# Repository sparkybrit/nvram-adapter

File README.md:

# nvram-adapter

A battery-backed 1M × 8 SRAM board for a breadboard, in the place of the
[ROM/RAM breadboard adapter](https://github.com/sparkybrit/rom-ram-breadboard-adapter) when it carries a
Dallas DS1250AB NVRAM, which is no longer made.

- **U1**: Lyontek LY62W10248ML-55LLI, 1M × 8 SRAM in TSOP-II-44, the chip used on the
  [SRAM breadboard adapter](https://github.com/sparkybrit/sram-breadboard-adapter).
- **U2**: Maxim MAX6365PKA46+T: switches the SRAM to the coin cell when +5 V fails, and blocks chip enable below
  4.63 V, matching the DS1250AB's 4.62 V write protection.
- **BT1**: CR2032 in an MPD BU2032SM-BT-GTR holder.
- **J1, J2**: the ROM/RAM adapter's two 20-pin headers, in the same places and with the same pinout except for
  four pins: J1.20 carries A19 (not +5 V), J2.12 carries U2's open-drain `/RESET`, J2.15 is not connected and J2.18
  is a +5 V input. Every pin is named on the silkscreen.
- **J3**: a screw terminal for +5 V, for when it doesn't come from the breadboard on J2.18.
- **SW1**: a manual reset button on U2's `/MR`.
- **D1**: a power LED.

It is also the prototype for the NVRAM and reset circuit of the Sparky1 backplane's NVRAM card.

KiCad 10, four layers. Built for [Sparky1](https://github.com/sparkybrit/sparky1), a 68030 breadboard computer.

**Status:** schematic done, board placed but not yet routed.

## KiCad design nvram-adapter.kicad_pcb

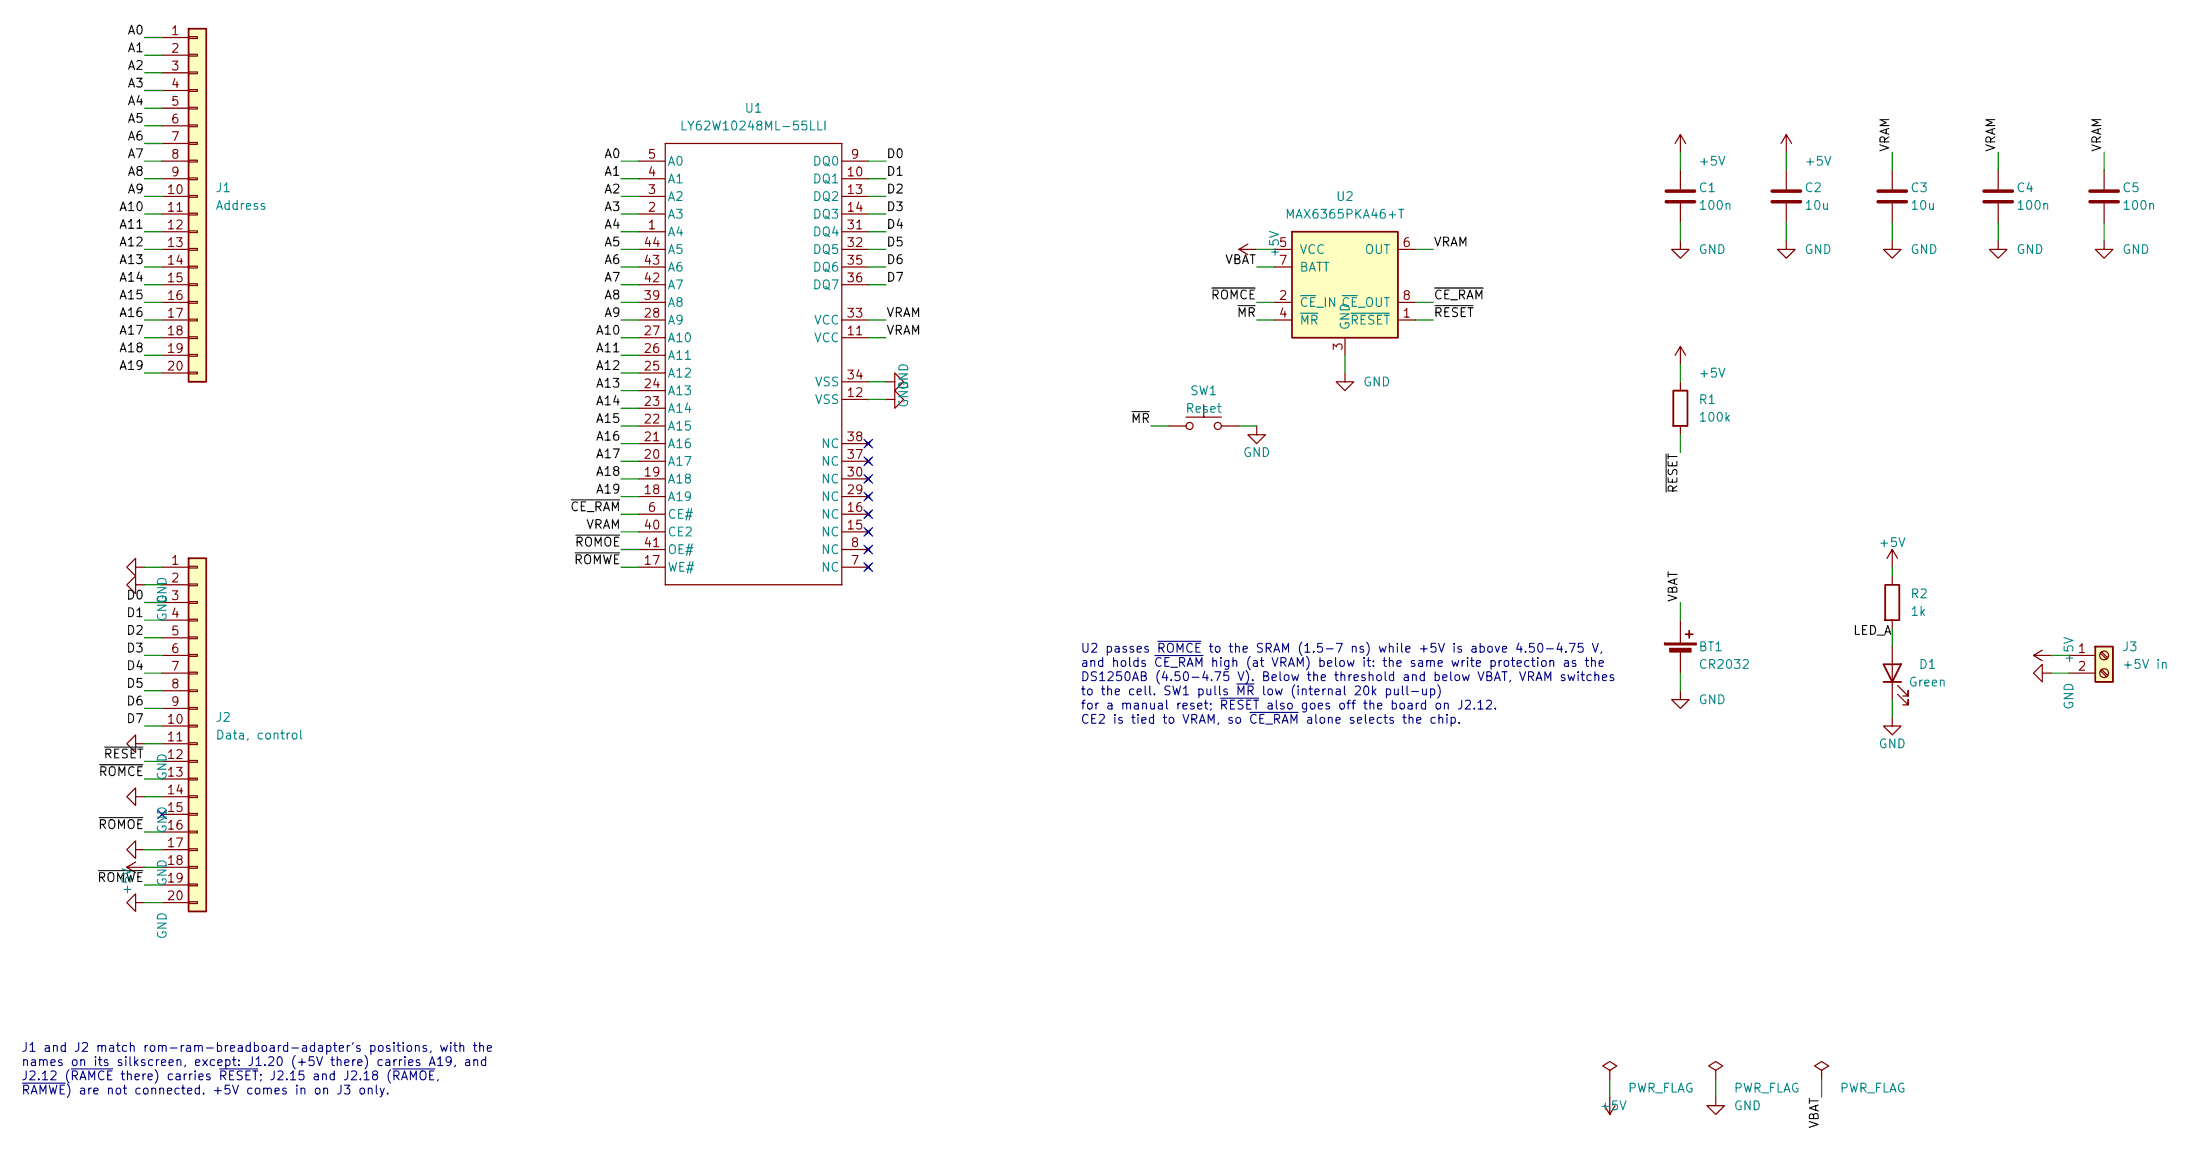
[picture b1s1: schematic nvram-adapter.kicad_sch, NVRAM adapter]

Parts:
BT1: CR2032; BatteryHolder_MPD_BU2032SM-BT_1x2032; MPN BU2032SM-BT-GTR
C1: 100n; C_0603_1608Metric
C2, C3: 10u; C_0805_2012Metric
C4, C5: 100n; C_0402_1005Metric
D1: Green; LED_0603_1608Metric
J1: Address; PinHeader_1x20_P2.54mm_Vertical
J2: Data, control; PinHeader_1x20_P2.54mm_Vertical
J3: +5V in; TerminalBlock_Phoenix_MKDS-1,5-2-5.08_1x02_P5.08mm_Horizont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
R1: 100k; R_0603_1608Metric
R2: 1k; R_0603_1608Metric
SW1: Reset; SW_SPST_PTS810
U1: LY62W10248ML-55LLI; TSOP-II-44_400MIL_LTK
U2: MAX6365PKA46+T; SOT-23-8

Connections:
+5V: C1.1, C2.1, J2.18, J3.1, R1.1, R2.1, U2.5 (VCC)
/A0: J1.1, U1.5 (A0)
/A1: J1.2, U1.4 (A1)
/A2: J1.3, U1.3 (A2)
/A3: J1.4, U1.2 (A3)
/A4: J1.5, U1.1 (A4)
/A5: J1.6, U1.44 (A5)
/A6: J1.7, U1.43 (A6)
/A7: J1.8, U1.42 (A7)
/A8: J1.9, U1.39 (A8)
/A9: J1.10, U1.28 (A9)
/A10: J1.11, U1.27 (A10)
/A11: J1.12, U1.26 (A11)
/A12: J1.13, U1.25 (A12)
/A13: J1.14, U1.24 (A13)
/A14: J1.15, U1.23 (A14)
/A15: J1.16, U1.22 (A15)
/A16: J1.17, U1.21 (A16)
/A17: J1.18, U1.20 (A17)
/A18: J1.19, U1.19 (A18)
/A19: J1.20, U1.18 (A19)
/D0: J2.3, U1.9 (DQ0)
/D1: J2.4, U1.10 (DQ1)
/D2: J2.5, U1.13 (DQ2)
/D3: J2.6, U1.14 (DQ3)
/D4: J2.7, U1.31 (DQ4)
/D5: J2.8, U1.32 (DQ5)
/D6: J2.9, U1.35 (DQ6)
/D7: J2.10, U1.36 (DQ7)
/LED_A: D1.2 (A), R2.2
/VBAT: BT1.1 (+), U2.7 (BATT)
/VRAM: C3.1, C4.1, C5.1, U1.11 (VCC), U1.33 (VCC), U1.40 (CE2), U2.6 (OUT)
/~CE_RAM: U1.6 (CE#), U2.8 (~CE_OUT)
/~MR: SW1.1, U2.4 (~MR)
/~RESET: J2.12, R1.2, U2.1 (~RESET)
/~ROMCE: J2.13, U2.2 (~CE_IN)
/~ROMOE: J2.16, U1.41 (OE#)
/~ROMWE: J2.19, U1.17 (WE#)
GND: BT1.2 (-), C1.2, C2.2, C3.2, C4.2, C5.2, D1.1 (K), J2.1, J2.2, J2.11, J2.14, J2.17, J2.20, J3.2, SW1.2, U1.12 (VSS), U1.34 (VSS), U2.3 (GND)

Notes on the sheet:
U2 passes ~{ROMCE} to the SRAM (1.5-7 ns) while +5V is above 4.50-4.75 V, and holds ~{CE_RAM} high (at VRAM) below it: the same write protection as the DS1250AB (4.50-4.75 V). Below the threshold and below VBAT, VRAM switches to the cell. SW1 pulls ~{MR} low (internal 20k pull-up) for a manual rese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
J1 and J2 match rom-ram-breadboard-adapter's positions, with the names on its silkscreen, except: J1.20 (+5V there) carries A19, and J2.12 (~{RAMCE} there) carries ~{RESET}; J2.15 and J2.18 (~{RAMOE}, ~{RAMWE}) are not connected. +5V comes in on J3 only.

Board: 4 copper layers, 15 parts (2 on the bottom side), 39 nets, no tracks yet.
